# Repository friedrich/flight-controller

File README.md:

# Flight controller

# Hardware features

- :heavy_check_mark: Voltage regulator delivering 3.3 V to the ICs
- :x: Battery voltage monitor
  - Battery voltage monitor pin PA10 is not connected to a DAC.
- :heavy_check_mark: Pulse width modulated power supply of the main and tail rotor motors
- :x: Current monitor of the main and tail rotor motors
  - Pins PF0 and PF1 are not connected to any operational amplifiers. This makes
    current sensing inaccurate, since the shunt voltage is quite low.
- :heavy_check_mark: PWM control of the swashplate servos
- :heavy_check_mark: Programming and debugging interface via SWD and SWO
- :heavy_check_mark: Linear acceleration sensor and gyroscope
- :x: GPS receiver
  - No usable signal from antenna.
  - There is no good return path for the antenna signal.
- :x: Radio module with support for BLE, LoRa, FLRC, GFSK and ranging
  - Untested.
  - There is no good return path for the antenna signal.
- :heavy_check_mark: RGB status indicator LED
- :heavy_check_mark: Overcurrent protection (fuse)

## Possible improvements

- Connect reset pins of other ICs to the microcontroller.
- Connect the SX1280 busy pin and multi-purpose digital I/O pins to the
  microcontroller.
- Connect one PIO pin of the GNSS receiver to the microcontroller for TX ready
  notification.
- Add test points to GND, CS, SDI, SDO, SCK, RESET.
- Print version number on the PCB.
- Remove silk screen labels of small compenents.
- Make it possible to manually pull up the BOOT0 pin in case the firmware
  disrupts SWD communication.
- The top internal layer should be a ground plane to ensure a nice return path
  for the RF signal. Make a six layer board with layers: signal, ground, signal,
  power, signal, ground.

# GPIO pins

| Pin  | Function   | Configuration |
|------|------------|---------------|
| PA0  |            |               |
| PA1  | TAIL_CTL   | TIM15_CH1N    |
| PA2  | LEFT_CTL   | TIM2_CH3      |
| PA3  | /RADIO_CS  | output        |
| PA4  | /ACCEL_CS  | output        |
| PA5  | SCK        | SPI1_SCK      |
| PA6  | SDI        | SPI1_MISO     |
| PA7  | SDO        | SPI1_MOSI     |
| PA8  |            |               |
| PA9  |            |               |
| PA10 | BATT_MON   |               |
| PA11 | RIGHT_CTL  | TIM4_CH1      |
| PA12 | BACK_CTL   | TIM4_CH2      |
| PA13 | SWDIO      | SWDIO         |
| PA14 | SWCLK      | SWCLK         |
| PA15 |            |               |
| PB0  | /GNSS_CS   | output        |
| PB3  | SWO        | TRACESWO      |
| PB4  | LED_R      | TIM3_CH1      |
| PB5  | LED_G      | TIM3_CH2      |
| PB6  | MAIN_CTL   | TIM16_CH1N    |
| PB7  | LED_B      | TIM3_CH4      |
| PF0  | MAIN_SENSE | ADC1_IN10     |
| PF1  | TAIL_SENSE | ADC2_IN10     |

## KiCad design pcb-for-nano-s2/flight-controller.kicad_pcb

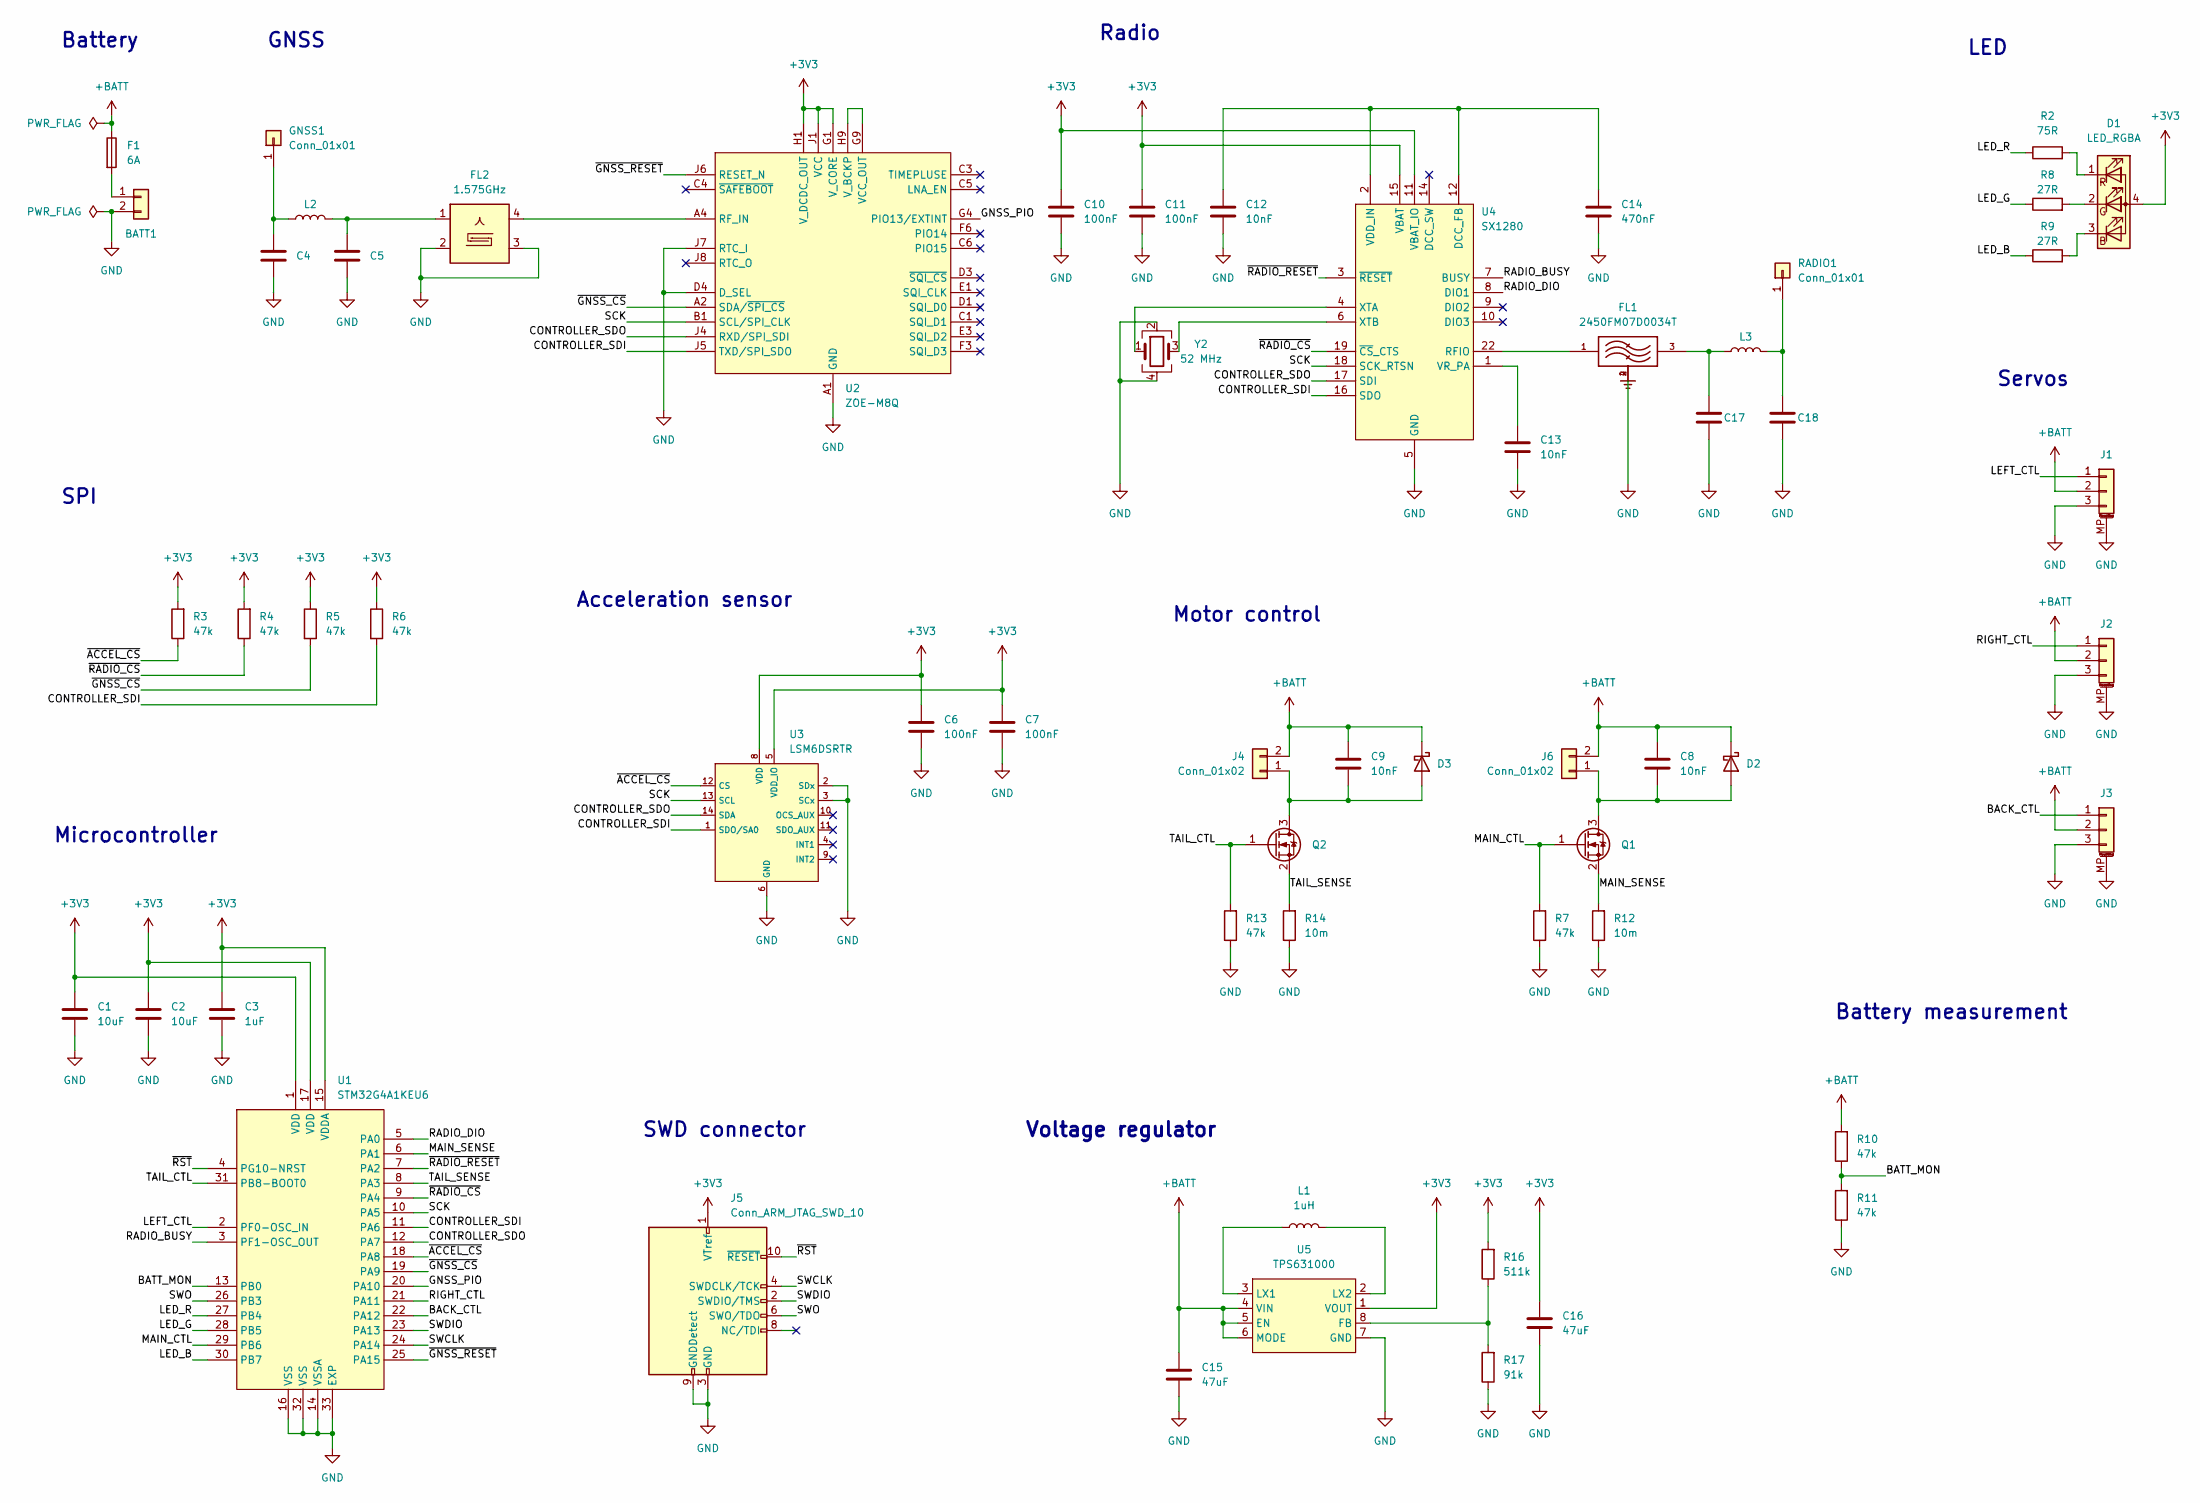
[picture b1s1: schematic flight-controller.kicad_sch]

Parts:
BATT1: Conn_01x02; Conn
C1, C2: 10uF; C_0402_1005Metric; MPN GRM155R60J106ME15D
C3: 1uF; C_0402_1005Metric; MPN CL05A105MQ5NNNC
C4, C5, C17, C18: C_0402_1005Metric
C6, C7, C10, C11: 100nF; C_0402_1005Metric; MPN CL05A104KA5NNNC
C8, C9, C12, C13: 10nF; C_0402_1005Metric; MPN CL05B103KB5NNNC
C14: 470nF; C_0402_1005Metric; MPN CL05A474KP5NNNC
C15, C16: 47uF; C_0603_1608Metric; MPN GRM188R60J476ME15D
D1: LED_RGBA; LED_156125M173000; MPN 156125M173000
D2, D3: D_Schottky; D_0402_1005Metric; MPN RB521S-30L2-TP
F1: 6A; Fuse_0603_1608Metric; MPN 0686F6000-01
FL1: 2450FM07D0034T; FIL_2450FM07D0034T; MPN 2450FM07D0034T
FL2: 1.575GHz; Filter_1411-5_1.4x1.1mm; MPN AFS14A04-1575.42-T3
GNSS1: Conn_01x01; Antenna
J1, J2, J3: BM03B-SRSS-TBLFSN; JST_SH_BM03B-SRSS-TB_1x03-1MP_P1.00mm_Vertical; MPN CI1103M1VR0-NH
J4: Conn_01x02; PinHeader_1x02_P1.27mm_Vertical; MPN 851-87-002-10-001101
J5: Conn_ARM_JTAG_SWD_10; PinHeader_2x05_P1.27mm_Vertical; MPN GRPB052VWVN-RC
J6: Conn_01x02; Molex_PicoBlade_53047-0210_1x02_P1.25mm_Vertical; MPN 0530470210
L1: 1uH; 0806; MPN DFE201612E-1R0M=P2
L2, L3: L_0402_1005Metric
Q1, Q2: Q_NMOS_GSD; SOT-23; MPN IRLML6244TRPBF
R2: 75R; R_0402_1005Metric; MPN RC0402JR-0775RL
R3, R4, R5, R6, R7, R10, R11, R13: 47k; R_0402_1005Metric; MPN RC0402JR-0747KL
R8, R9: 27R; R_0402_1005Metric; MPN RC0402JR-0727RL
R12, R14: 10m; R_0402_1005Metric; MPN ERJ-2LWFR010X
R16: 511k; R_0402_1005Metric; MPN RC0402FR-07511KL
R17: 91k; R_0402_1005Metric; MPN RC0402FR-0791KL
RADIO1: Conn_01x01; Antenna
U1: STM32G4A1KEU6; UFQFPN-32-1EP_5x5mm_P0.5mm_EP3.5x3.5mm; MPN STM32G4A1KEU6
U2: ZOE-M8Q; componentsearchengine-BGA51C50P9X9_450X450X110; MPN ZOE-M8Q-0
U3: LSM6DSRTR; LGA-14_3x2.5mm; MPN LSM6DSRTR
U4: SX1280; HVQFN-24-1EP_4x4mm_P0.5mm_EP2.6x2.6mm; MPN SX1280IMLTRT
U5: TPS631000; SC-70-8; MPN TPS631000DRLR
Y2: 52 MHz; XTAL_ECS-520-8-47-CKM-TR; MPN ECS-520-8-47-CKM-TR

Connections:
+3V3: C1.1, C2.1, C3.1, C6.1, C7.1, C10.1, C11.1, C16.1, D1.4 (A), J5.1 (VTref), R3.2, R4.2, R5.1, R6.1, R16.2, U1.1 (VDD), U1.15 (VDDA), U1.17 (VDD), U2.G1 (V_CORE), U2.H1 (V_DCDC_OUT), U2.J1 (VCC), U2.J2 (VCC), U3.5 (VDD_IO), U3.8 (VDD), U4.11 (VBAT_IO), U4.15 (VBAT), U5.1 (VOUT)
+BATT: C8.1, C9.1, C15.1, D2.1 (K), D3.1 (K), F1.1, J1.2, J2.2, J3.2, J4.2, J6.2, R10.2, U5.4 (VIN), U5.5 (EN), U5.6 (MODE)
/BACK_CTL: J3.1, U1.22 (PA12)
/BATT_MON: R10.1, R11.2, U1.13 (PB0)
/CONTROLLER_SDI: R6.2, U1.11 (PA6), U2.J5 (TXD/SPI_SDO), U3.1 (SDO/SA0), U4.16 (SDO)
/CONTROLLER_SDO: U1.12 (PA7), U2.J4 (RXD/SPI_SDI), U3.14 (SDA), U4.17 (SDI)
/GNSS_PIO: U1.20 (PA10), U2.G4 (PIO13/EXTINT)
/LED_B: R9.1, U1.30 (PB7)
/LED_G: R8.1, U1.28 (PB5)
/LED_R: R2.1, U1.27 (PB4)
/LEFT_CTL: J1.1, U1.2 (PF0-OSC_IN)
/MAIN_CTL: Q1.1 (G), R7.2, U1.29 (PB6)
/MAIN_SENSE: Q1.2 (S), R12.2, U1.6 (PA1)
/RADIO_BUSY: U1.3 (PF1-OSC_OUT), U4.7 (BUSY)
/RADIO_DIO: U1.5 (PA0), U4.8 (DIO1)
/RIGHT_CTL: J2.1, U1.21 (PA11)
/SCK: U1.10 (PA5), U2.B1 (SCL/SPI_CLK), U3.13 (SCL), U4.18 (SCK_RTSN)
/SWCLK: J5.4 (SWDCLK/TCK), U1.24 (PA14)
/SWDIO: J5.2 (SWDIO/TMS), U1.23 (PA13)
/SWO: J5.6 (SWO/TDO), U1.26 (PB3)
/TAIL_CTL: Q2.1 (G), R13.2, U1.31 (PB8-BOOT0)
/TAIL_SENSE: Q2.2 (S), R14.2, U1.8 (PA3)
/~ACCEL_CS: R3.1, U1.18 (PA8), U3.12 (CS)
/~GNSS_CS: R5.2, U1.19 (PA9), U2.A2 (SDA/~SPI_CS)
/~GNSS_RESET: U1.25 (PA15), U2.J6 (RESET_N)
/~RADIO_CS: R4.1, U1.9 (PA4), U4.19 (~CS_CTS)
/~RADIO_RESET: U1.7 (PA2), U4.3 (~RESET)
/~RST: J5.10 (~RESET), U1.4 (PG10-NRST)
GND: BATT1.2, C1.2, C2.2, C3.2, C4.1, C5.1, C6.2, C7.2, C10.2, C11.2, C12.2, C13.2, C14.2, C15.2, C16.2, C17.1, C18.1, FL1.2, FL1.4, FL2.2, FL2.3, FL2.5, J1.3, J1.MP (MountPin), J2.3, J2.MP (MountPin), J3.3, J3.MP (MountPin), J5.3 (GND), J5.5 (GND), J5.9 (GNDDetect), R7.1, R11.1, R12.1, R13.1, R14.1, R17.1, U1.14 (VSSA), U1.16 (VSS), U1.32 (VSS), U1.33 (EXP), U2.A1 (GND), U2.A3 (GND), U2.A5 (GND), U2.A7 (GND), U2.A8 (GND), U2.A9 (GND), U2.B9 (GND), U2.C7 (GND), U2.C9 (GND), U2.D4 (D_SEL), U2.D6 (GND), U2.D9 (GND), U2.E7 (GND), U2.F7 (GND), U2.G3 (GND), U2.G6 (GND), U2.G7 (GND), U2.J3 (GND), U2.J7 (RTC_I), U2.J9 (GND), U3.2 (SDx), U3.3 (SCx), U3.6 (GND), U3.7 (GND), U4.5 (GND), U4.13 (GND), U4.20 (GND), U4.21 (GND), U4.23 (GND), U4.24 (GND), U4.25 (GND), U5.7 (GND), Y2.2, Y2.4
unnamed: BATT1.1, F1.2
unnamed: C5.2, FL2.1, L2.2
unnamed: C17.2, FL1.3, L3.1
unnamed: D1.3 (BK), R9.2
unnamed: D1.2 (GK), R8.2
unnamed: D1.1 (RK), R2.2
unnamed: C8.2, D2.2 (A), J6.1, Q1.3 (D)
unnamed: C9.2, D3.2 (A), J4.1, Q2.3 (D)
unnamed: C4.2, GNSS1.1, L2.1
unnamed: C18.2, L3.2, RADIO1.1
unnamed: FL2.4, U2.A4 (RF_IN)
unnamed: U2.G9 (VCC_OUT), U2.H9 (V_BCKP)
unnamed: C12.1, C14.1, U4.2 (VDD_IN), U4.12 (DCC_FB)
unnamed: FL1.1, U4.22 (RFIO)
unnamed: C13.1, U4.1 (VR_PA)
unnamed: U4.4 (XTA), Y2.1
unnamed: U4.6 (XTB), Y2.3
unnamed: R16.1, R17.2, U5.8 (FB)
unnamed: L1.1, U5.3 (LX1)
unnamed: L1.2, U5.2 (LX2)

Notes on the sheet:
Acceleration sensor
Microcontroller
Battery
GNSS
SWD connector
Battery measurement
Radio
SPI
Voltage regulator
Motor control
LED
Servos

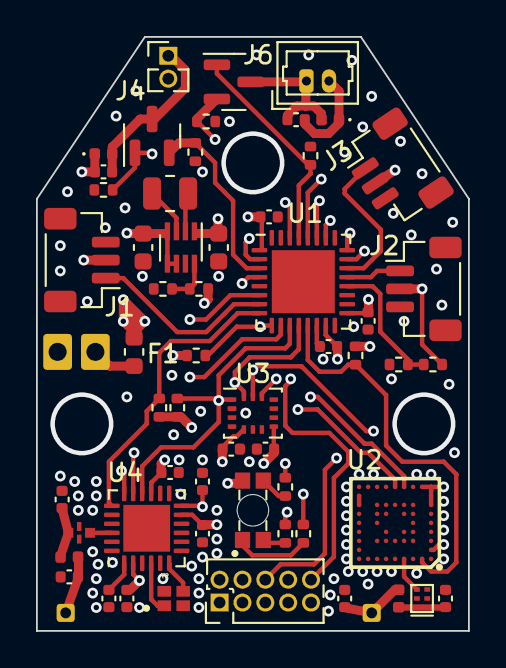
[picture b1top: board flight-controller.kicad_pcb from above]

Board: 6 copper layers, 24.0 x 33.0 mm, 59 parts (0 on the bottom side), 49 nets.

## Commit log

2023-01-18 add PCB
2023-01-18 add impedance matching circuits for antennas
2023-01-18 fix component infos
2023-01-18 remove solder mask expansion
2023-01-29 add README
2023-02-08 create empty firmware from cortex-m-quickstart
2023-02-08 update dependencies
2023-02-11 adapt device config
2023-02-11 adjust OpenOCD config
2023-02-11 add improvements to README
2023-02-13 rustfmt
2023-02-13 accelerometer test
2023-02-13 improve
2023-02-13 add radio (works when manually reset during idle time)
2023-02-13 enable ITM
2023-02-13 try transmitting (does not work)
2023-02-13 Squashed 'firmware/vendor/radio-sx128x/' content from commit 61fa993
    git-subtree-dir: firmware/vendor/radio-sx128x
    git-subtree-split: 61fa993a6f7a1287e3fbbe16772d33df90cca0e6
2023-02-13 fix radio-sx128x compilation
2023-02-13 somethinga
2023-02-13 use ITM for panics
2023-02-13 somewhat
2023-02-13 gyroscope
2023-02-13 use pin macros for LED
2023-02-14 GNSS (works sometimes)
2023-02-14 still the same
2023-02-14 some state handling
2023-02-14 update Kicad file version
2023-02-14 testi
2023-02-15 complete SPI disabling
2023-02-15 replace LED NPTH by via
2023-02-15 add UBX message types
2023-02-15 remove small component's labels
2023-02-15 gnss
2023-02-15 whaaaat - radio worked without reset
2023-02-16 read and write macro
2023-02-16 move RadioHal out of the way
2023-02-16 lots
2023-02-16 move
2023-02-17 disable NMEA
2023-02-17 init
2023-02-17 readme
2023-02-19 radio without library - tx works
2023-02-19 bluetooth - tx response with success
2023-02-19 loop
2023-02-19 disable radio code
2023-02-19 gnss led color
2023-02-19 clean up
2023-02-19 clean up more
2023-02-19 add motors
2023-02-19 move code
2023-02-20 improve pins macros
2023-02-20 use op amp
2023-02-20 unfill zones
2023-02-22 update PCB from schematic
2023-02-22 remove small components' labels
2023-02-22 change PCB design to six layers
2023-02-22 add TODO
2023-02-23 fix connections and add new ones in schematic
